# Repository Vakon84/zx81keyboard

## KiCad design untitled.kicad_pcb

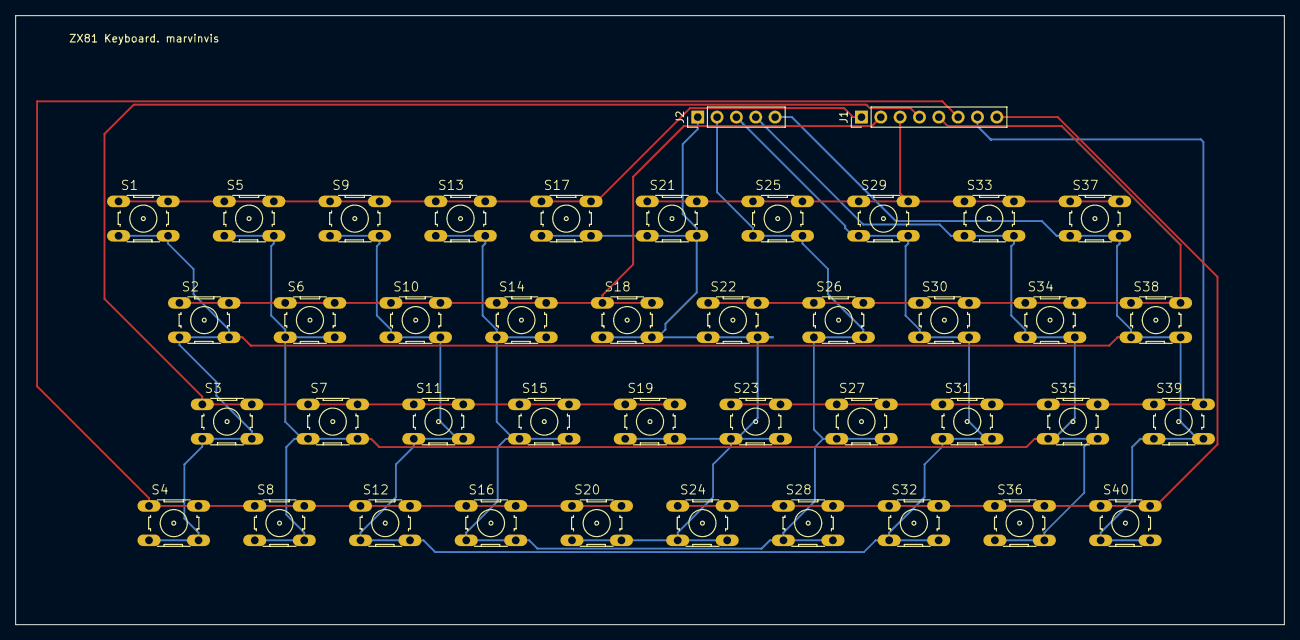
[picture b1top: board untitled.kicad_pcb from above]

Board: 2 copper layers, 166.7 x 80.0 mm, 42 parts (0 on the bottom side), 13 nets.

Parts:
J1: 66100811622; PinHeader_1x08_P2.54mm_Vertical
J2: 66100511722; PinHeader_1x05_P2.54mm_Vertical
S1: 1; B3F-10XX
S2: Q; B3F-10XX
S3: A; B3F-10XX
S4: SH; B3F-10XX
S5: 2; B3F-10XX
S6: W; B3F-10XX
S7: S; B3F-10XX
S8: Z; B3F-10XX
S9: 3; B3F-10XX
S10: E; B3F-10XX
S11: D; B3F-10XX
S12: X; B3F-10XX
S13: 4; B3F-10XX
S14: R; B3F-10XX
S15: F; B3F-10XX
S16: C; B3F-10XX
S17: 5; B3F-10XX
S18: T; B3F-10XX
S19: G; B3F-10XX
S20: V; B3F-10XX
S21: 6; B3F-10XX
S22: Y; B3F-10XX
S23: H; B3F-10XX
S24: B; B3F-10XX
S25: 7; B3F-10XX
S26: U; B3F-10XX
S27: J; B3F-10XX
S28: N; B3F-10XX
S29: 8; B3F-10XX
S30: I; B3F-10XX
S31: K; B3F-10XX
S32: M; B3F-10XX
S33: 9; B3F-10XX
S34: O; B3F-10XX
S35: L; B3F-10XX
S36: DOT; B3F-10XX
S37: ZERO; B3F-10XX
S38: P; B3F-10XX
S39: NL; B3F-10XX
S40: SP; B3F-10XX

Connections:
/A8: J1.6, S4.1, S4.2, S8.1, S8.2, S12.1, S12.2, S16.1, S16.2, S20.1, S20.2
/A9: J1.4, S3.1, S3.2, S7.1, S7.2, S11.1, S11.2, S15.1, S15.2, S19.1, S19.2
/A10: J1.2, S2.1, S2.2, S6.1, S6.2, S10.1, S10.2, S14.1, S14.2, S18.1, S18.2
/A11: J1.1, S1.1, S1.2, S5.1, S5.2, S9.1, S9.2, S13.1, S13.2, S17.1, S17.2
/A12: J1.3, S21.1, S21.2, S25.1, S25.2, S29.1, S29.2, S33.1, S33.2, S37.1, S37.2
/A13: J1.5, S22.1, S22.2, S26.1, S26.2, S30.1, S30.2, S34.1, S34.2, S38.1, S38.2
/A14: J1.7, S23.1, S23.2, S27.1, S27.2, S31.1, S31.2, S35.1, S35.2, S39.1, S39.2
/A15: J1.8, S24.1, S24.2, S28.1, S28.2, S32.1, S32.2, S36.1, S36.2, S40.1, S40.2
/D0: J2.5, S1.3, S1.4, S2.3, S2.4, S3.3, S3.4, S4.3, S4.4, S37.3, S37.4, S38.3, S38.4, S39.3, S39.4, S40.3, S40.4
/D1: J2.4, S5.3, S5.4, S6.3, S6.4, S7.3, S7.4, S8.3, S8.4, S33.3, S33.4, S34.3, S34.4, S35.3, S35.4, S36.3, S36.4
/D2: J2.3, S9.3, S9.4, S10.3, S10.4, S11.3, S11.4, S12.3, S12.4, S29.3, S29.4, S30.3, S30.4, S31.3, S31.4, S32.3, S32.4
/D3: J2.2, S13.3, S13.4, S14.3, S14.4, S15.3, S15.4, S16.3, S16.4, S25.3, S25.4, S26.3, S26.4, S27.3, S27.4, S28.3, S28.4
/D4: J2.1, S17.3, S17.4, S18.3, S18.4, S19.3, S19.4, S20.3, S20.4, S21.3, S21.4, S22.3, S22.4, S23.3, S23.4, S24.3, S24.4

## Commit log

2019-07-08 initial schema and pcb
